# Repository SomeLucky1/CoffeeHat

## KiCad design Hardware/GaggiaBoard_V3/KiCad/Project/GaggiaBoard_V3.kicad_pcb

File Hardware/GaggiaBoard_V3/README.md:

# Gaggiuino board

Gaggiuino hardware controller board v3 - WIP

[3D model](https://github.com/banoz/banoz.github.io/blob/main/repository/stl/GaggiaBoard_V3.stl)

```
J10, J11 - AC input
J12 - pump
J13 - 3-way valve

J1 - UART2 (PA2/PA3)
J2 - I2C
J4 - thermocouple
J6 - Pressure sensor (ADS101X/ADS111X on I2C1)
J7 - Brew (PC14) / Steam (PC15) switch
J8 - Scales (PB0 -> CLK, PB8 -> D1, PB9 -> D2)
J9 - 5V SSR control (PA15 -> SSR1, PA8 -> SSR2)

AC zero-cross sense on PA0
Pump control on PA1
3-Way valve control on PC13

SPI1 is used by thermocouple amplifier on PA5(SPI1_SCK)/PB4(SPI1_MISO), and CS on PA6

I2C port on PB6(I2C1_SCL)/PB7(I2C1_SDA)

J27 - USART1 (PA9/10) with NRST and BOOT1
```

Top|Bottom
---|---
|
|
|

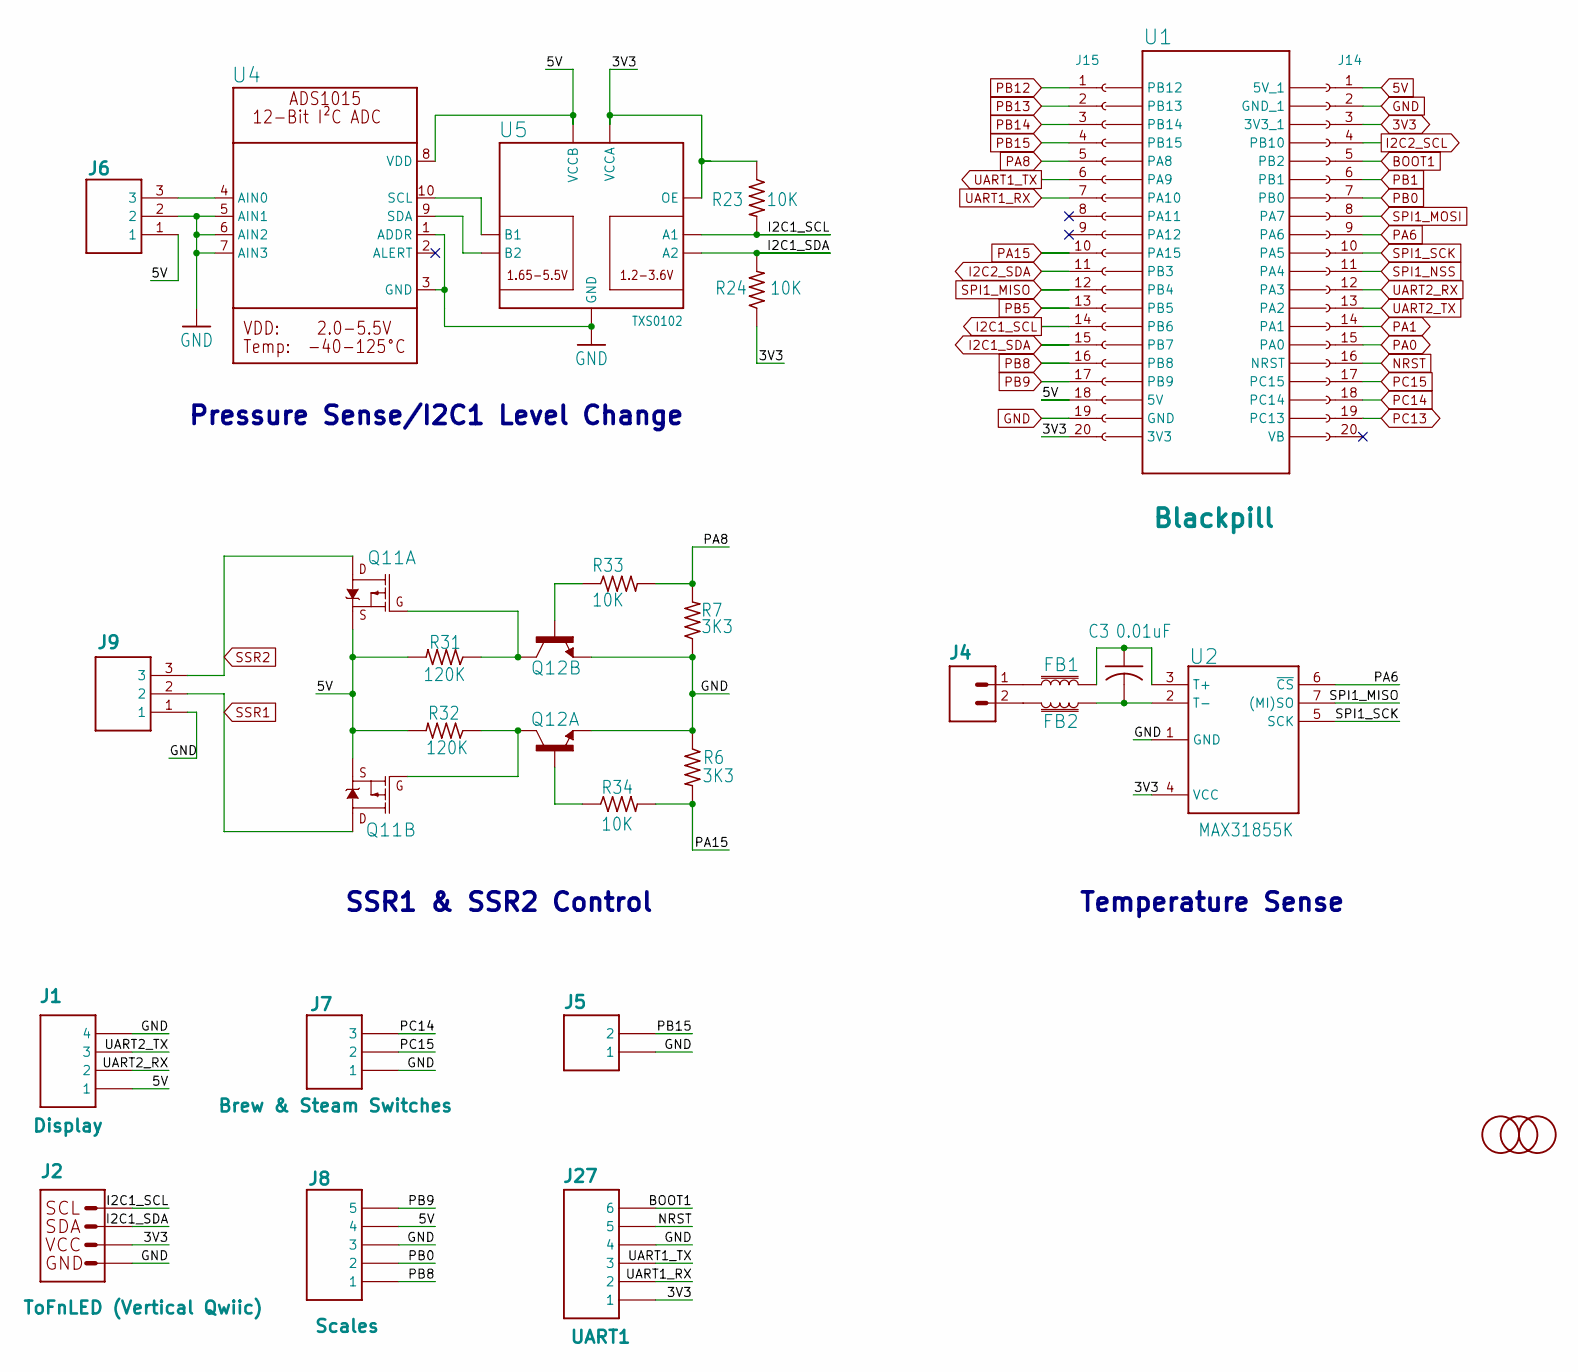
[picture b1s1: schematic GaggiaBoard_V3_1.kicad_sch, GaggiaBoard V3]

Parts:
C3: 0.01uF; C0603; LCSC C100042
FB1, FB2: FERRITE_BEAD-0603-470Ω-100MHZ-1A-200MILIΩ; 0603; LCSC C883591
J1: Display; B4B-PH-K-S; LCSC C131334
J2: ToFnLED (Vertical Qwiic); JST04_1MM_VERT; LCSC C160390
J4: TC Sensor; SCREWTERMINAL-3.5MM-2-NS; LCSC C474892
J5: 2PIN; B2B-PH-K-S; LCSC C131337
J6: Pressure TD; B3B-PH-K-S; LCSC C131339
J7: Brew & Steam Switches; B3B-PH-K-S; LCSC C131339
J8: Scales; B5B-PH-K-S; LCSC C157993
J9: SSR; B3B-PH-K-S; LCSC C131339
J14, J15: 1x20 Female Header 2.54mm; 1x20_P2.54mm_Female_Vertical
J27: UART1; B6B-PH-K-S; LCSC C131342
MARK1, MARK2, MARK5: FIDUCIAL; FIDUCIAL_1MM
Q11: MOSFET_PCH_DUAL-DMP2240UDM; SOT26; LCSC C397948
Q12: TRANS_NPN_DUAL-MBT3904DW1T1; SC70-6; LCSC C896759
R6, R7: 3K3; R0603; LCSC C114432
R23, R24, R33, R34: 10K; R0603; LCSC C98220
R31, R32: 120K; R0603; LCSC C114607
U1: Blackpill; BLACKPILL
U2: MAX31855K; SO08; LCSC C52028
U4: ADC_ADS1015; MSOP10; LCSC C193969
U5: TXS0102; VFSOP-8; LCSC C53434

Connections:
3V3: J2.2, J14.3, J15.20, J27.1, R23.1, R24.1, U2.4 (VCC), U5.P$3 (VCCA), U5.P$6 (OE); also elsewhere on the board
5V: J1.1, J6.1, J8.4, J14.1, J15.18, Q11.S1 (S), Q11.S2 (S), R31.2, R32.2, U4.8 (VDD), U5.P$7 (VCCB); also elsewhere on the board
BOOT1: J14.5, J27.6
GND: J1.4, J2.1, J5.1, J6.2, J7.1, J8.3, J9.1, J14.2, J15.19, J27.4, Q12.1 (E), Q12.4 (E), R6.1, R7.1, U2.1 (GND), U4.1 (ADDR), U4.3 (GND), U4.5 (AIN1), U4.6 (AIN2), U4.7 (AIN3), U5.P$2 (GND); also elsewhere on the board
I2C1_SCL: J2.4, J15.14, R23.2, U5.P$5 (A1)
I2C1_SDA: J2.3, J15.15, R24.2, U5.P$4 (A2)
I2C2_SCL: J14.4
I2C2_SDA: J15.11
NRST: J14.16, J27.5
unnamed: FB1.1, J4.1
unnamed: FB2.1, J4.2
unnamed: Q11.G1 (G), Q12.6 (C), R31.1
unnamed: Q11.G2 (G), Q12.3 (C), R32.1
unnamed: Q12.5 (B), R34.1
unnamed: Q12.2 (B), R33.1
unnamed: C3.1, FB1.2, U2.3 (T+)
unnamed: C3.2, FB2.2, U2.2 (T-)
unnamed: J6.3, U4.4 (AIN0)
unnamed: U4.10 (SCL), U5.P$8 (B1)
unnamed: U4.9 (SDA), U5.P$1 (B2)
PA0: J14.15; also elsewhere on the board
PA1: J14.14; also elsewhere on the board
PA6: J14.9, U2.6 (~CS)
PA8: J15.5, R7.2, R33.2
PA15: J15.10, R6.2, R34.2
PB0: J8.2, J14.7
PB1: J14.6
PB5: J15.13
PB8: J8.1, J15.16
PB9: J8.5, J15.17
PB12: J15.1
PB13: J15.2
PB14: J15.3
PB15: J5.2, J15.4
PC13: J14.19; also elsewhere on the board
PC14: J7.3, J14.18
PC15: J7.2, J14.17
SPI1_MISO: J15.12, U2.7 ((MI)SO)
SPI1_MOSI: J14.8
SPI1_NSS: J14.11
SPI1_SCK: J14.10, U2.5 (SCK)
SSR1: J9.2, Q11.D2 (D)
SSR2: J9.3, Q11.D1 (D)
UART1_RX: J15.7, J27.2
UART1_TX: J15.6, J27.3
UART2_RX: J1.2, J14.12
UART2_TX: J1.3, J14.13

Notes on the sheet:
Pressure Sense/I2C1 Level Change
SSR1 & SSR2 Control
Temperature Sense

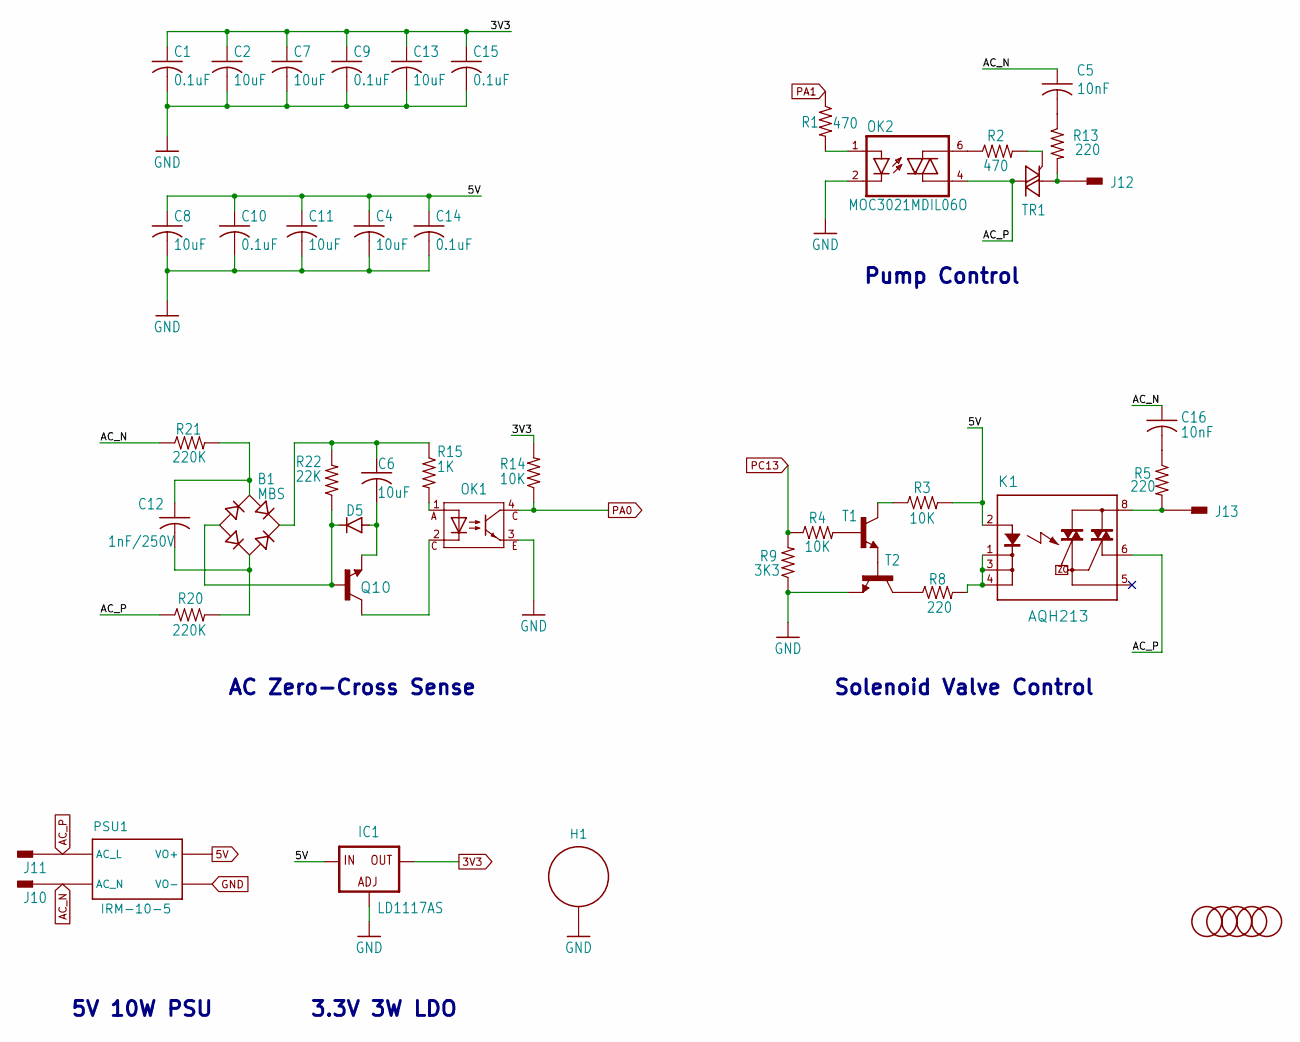
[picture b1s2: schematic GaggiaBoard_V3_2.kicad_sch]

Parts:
B1: MBS; SOIC-4; LCSC C2487
C1, C9, C10, C14, C15: 0.1uF; C0603; LCSC C1591
C2, C4, C6, C7, C8, C11, C13: 10uF; C0603; LCSC C86275
C5, C16: 10nF; C1206; LCSC C107192
C12: 1nF/250V; C0603; LCSC C277510
D5: 1N4007; DO214AC; LCSC C727081
H1: STANDOFF_ELECTRICAL; STANDOFF-ELECTRICAL
IC1: LD1117AS; SOT223; LCSC C26537
J10, J11, J12, J13: PIN262409-1; 62409-1; LCSC C86495
K1: AQH213; DIL07; LCSC C719560
MARK3, MARK4, MARK6, MARK7, MARK8: FIDUCIAL; FIDUCIAL_1MM
OK1: WL-OCPT_SERIES_101X; WL-OCPT_LSOP4; LCSC C141610
OK2: MOC3021MDIL06O; DIL06O; LCSC C5242
PSU1: IRM-10-5; IRM-10; LCSC C2857903
Q10: TRANS_NPN-MMBT2222AL; SOT23-3; LCSC C82460
R1, R2: 470; R0603; LCSC C114669
R3, R4, R14: 10K; R0603; LCSC C98220
R5, R13: 220; R2512; LCSC C877859
R8: 220; R0603; LCSC C107696
R9: 3K3; R0603; LCSC C114432
R15: 1K; R0603; LCSC C22548
R20, R21: 220K; R1206; LCSC C130275
R22: 22K; R0603; LCSC C114065
T1, T2: -NPN-SOT23-BEC; SOT23-BEC; LCSC C82460
TR1: Z0107MNSOT-223; SOT223; LCSC C71218

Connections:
3V3: C1.1, C2.1, C7.1, C9.1, C13.1, C15.1, IC1.4 (OUT), R14.2; also elsewhere on the board
5V: C4.1, C8.1, C10.1, C11.1, C14.1, IC1.3 (IN), K1.2 (A), PSU1.+V (VO+), R3.2; also elsewhere on the board
AC_N: C5.1, C16.1, J10.A1 (1), J10.A2 (1), PSU1.AC/N (AC_N), R21.1
AC_P: J11.A1 (1), J11.A2 (1), K1.6 (DS3), OK2.4 (A1), PSU1.AC/L (AC_L), R20.1, TR1.2 (A2), TR1.4 (A2)
GND: C1.2, C2.2, C4.2, C7.2, C8.2, C9.2, C10.2, C11.2, C13.2, C14.2, C15.2, H1.P1, IC1.1 (ADJ), OK1.3, OK2.2 (C), PSU1.-V (VO-), R9.1, T2.E; also elsewhere on the board
unnamed: B1.~1 (AC1), C12.2, R20.2
unnamed: B1.~2 (AC2), C12.1, R21.2
unnamed: B1.+, C6.1, R15.1, R22.2
unnamed: C5.2, R13.1
unnamed: C16.2, R5.1
unnamed: J13.A1 (1), J13.A2 (1), K1.8 (DS1), R5.2
unnamed: K1.1 (K), K1.3 (K1), K1.4 (K2), R8.2
unnamed: OK1.1, R15.2
unnamed: OK2.6 (A2), R2.1
unnamed: OK2.1 (A), R1.2
unnamed: B1.-, D5.C, Q10.1 (B), R22.1
unnamed: OK1.2, Q10.3 (C)
unnamed: C6.2, D5.A, Q10.2 (E)
unnamed: R3.1, T1.C
unnamed: R4.2, T1.B
unnamed: R8.1, T2.C
unnamed: T1.E, T2.B
unnamed: J12.A1 (1), J12.A2 (1), R13.2, TR1.1 (A1)
unnamed: R2.2, TR1.3 (G)
PA0: OK1.4, R14.1; also elsewhere on the board
PA1: R1.1; also elsewhere on the board
PC13: R4.1, R9.2; also elsewhere on the board

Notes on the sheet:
5V 10W PSU
AC Zero-Cross Sense
Solenoid Valve Control
Pump Control
3.3V 3W LDO

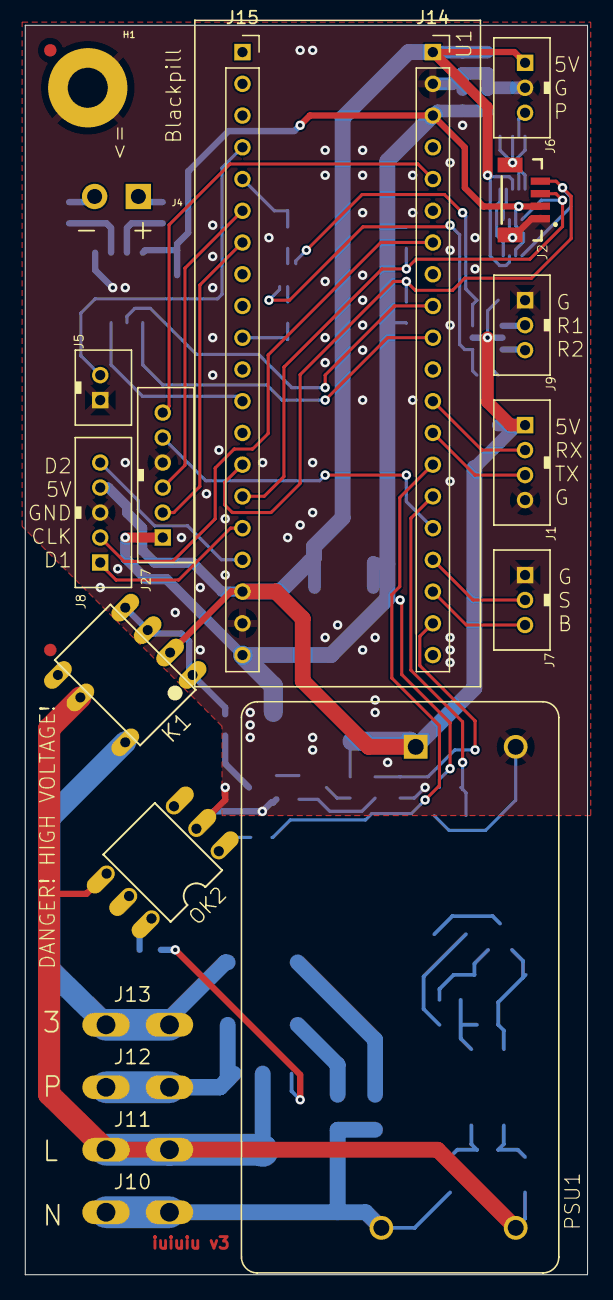
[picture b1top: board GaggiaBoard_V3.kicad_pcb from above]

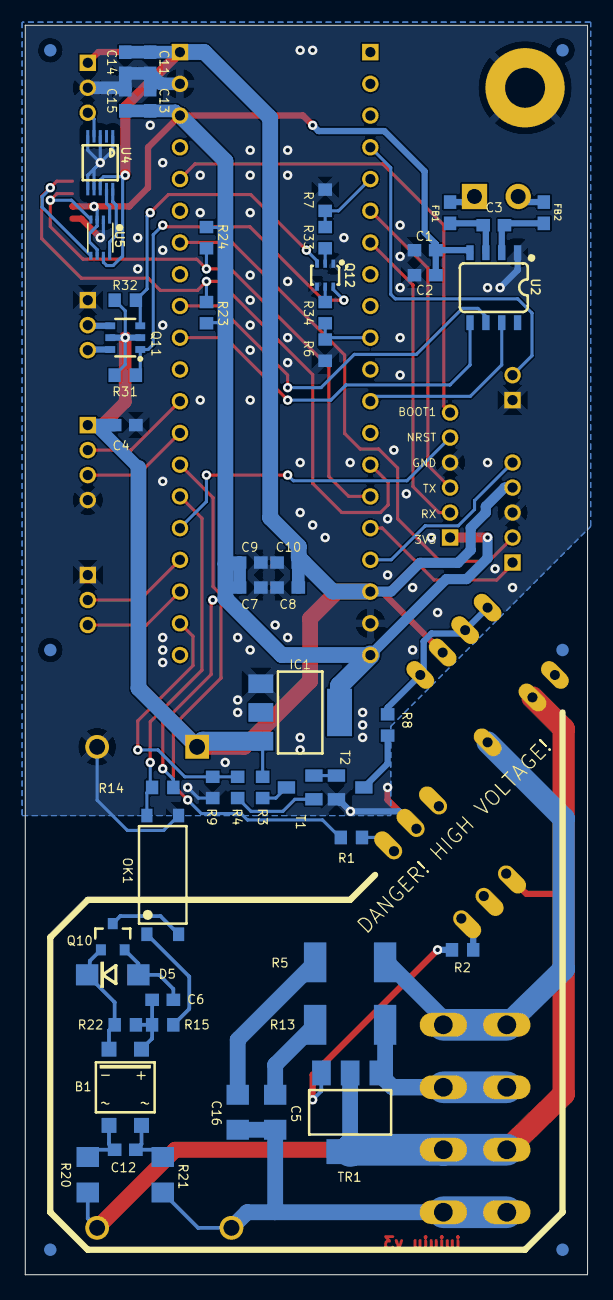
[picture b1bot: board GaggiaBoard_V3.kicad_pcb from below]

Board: 2 copper layers, 45.0 x 100.0 mm, 80 parts (58 on the bottom side), 59 nets.

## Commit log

2023-09-08 Adding converted KiCad project assets
2023-09-08 brighten 3d renders
2023-09-08 More details
2023-09-08 Get all the angles
2023-09-10 3D PSU model label
2023-09-10 KiCad project and model updates
